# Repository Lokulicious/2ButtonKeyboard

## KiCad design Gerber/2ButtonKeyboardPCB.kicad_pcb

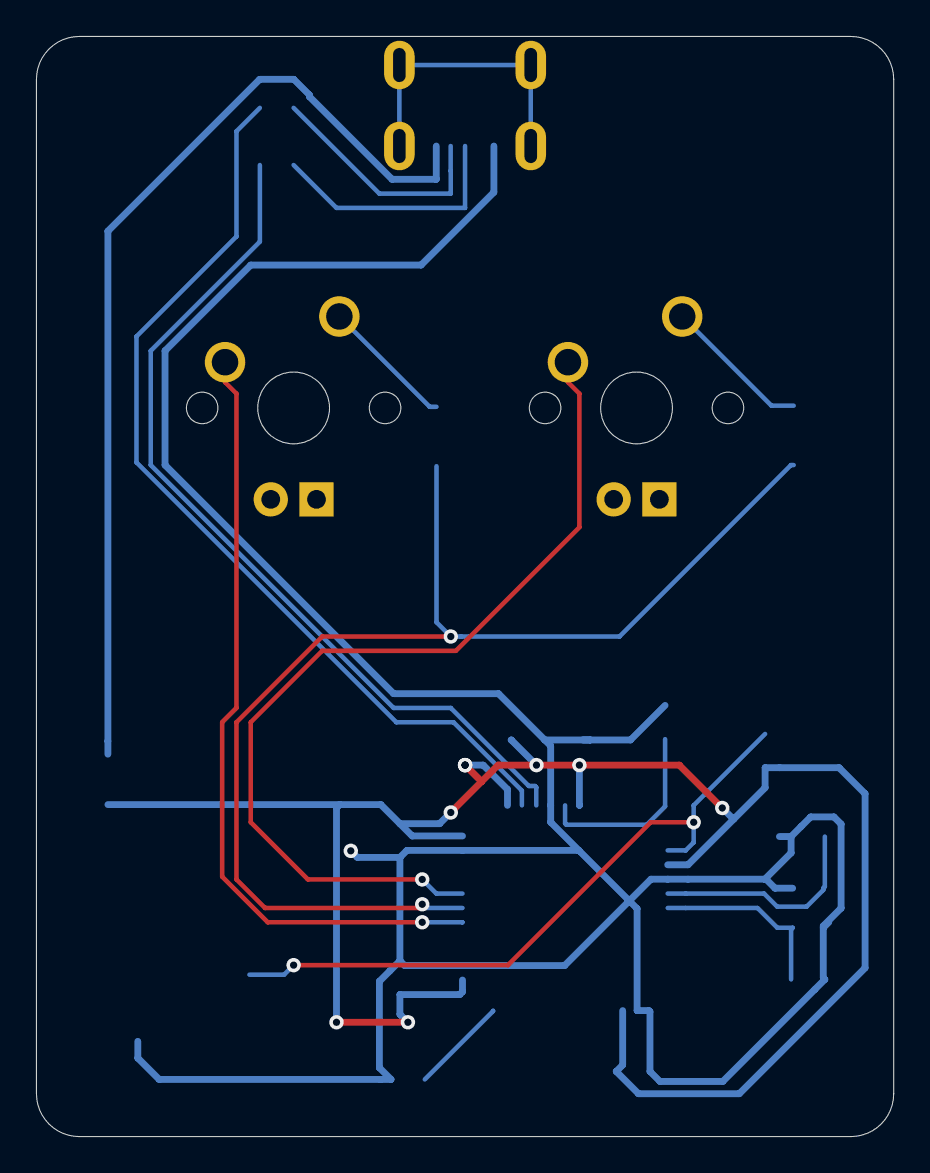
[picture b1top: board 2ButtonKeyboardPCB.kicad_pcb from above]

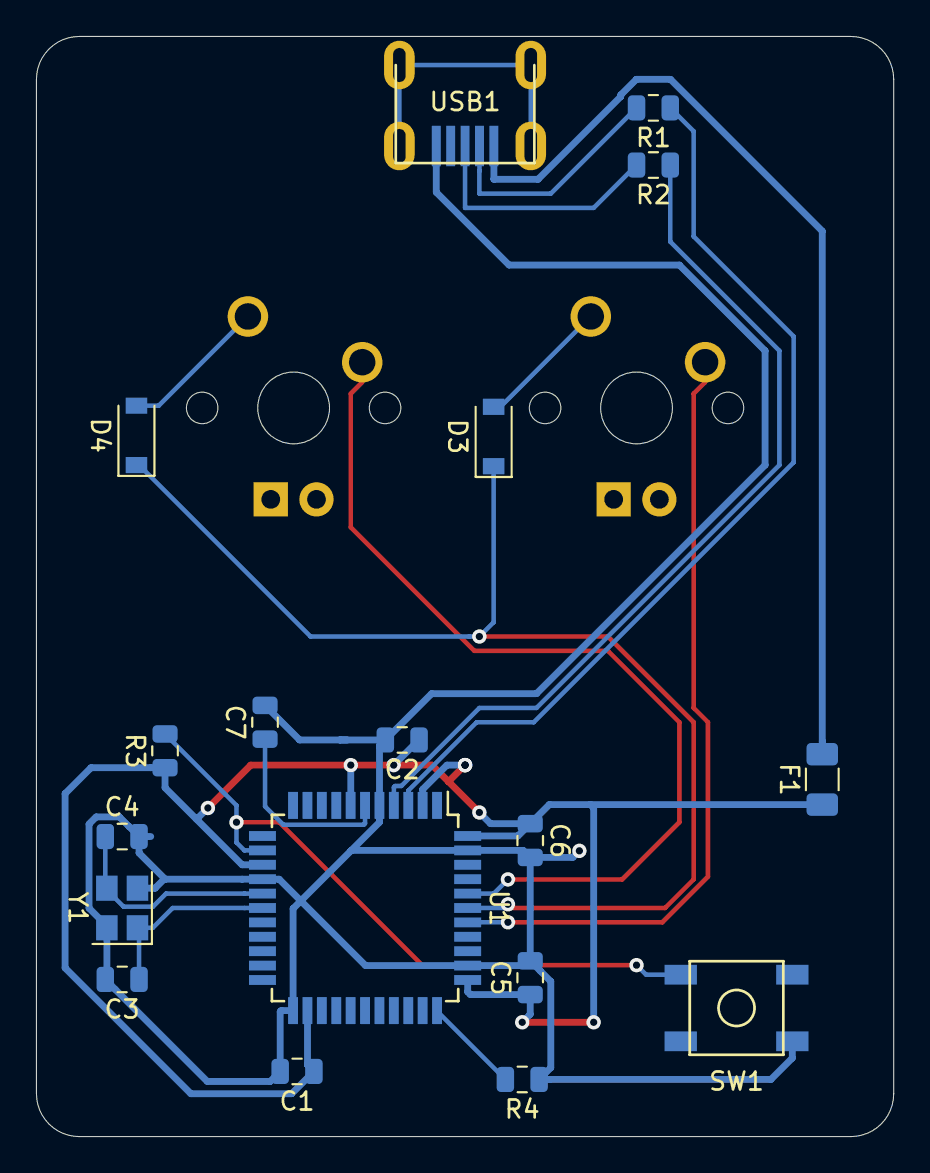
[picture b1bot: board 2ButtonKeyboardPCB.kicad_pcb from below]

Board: 2 copper layers, 47.6 x 61.1 mm, 20 parts (18 on the bottom side), 17 nets.

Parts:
C1, C2, C5: 0.1uF; C_0805_2012Metric
C3, C4: 22pF; C_0805_2012Metric
C6: 10uF; C_0805_2012Metric
C7: 1uF; C_0805_2012Metric
D3, D4: D_Small; D_SOD-123
F1: Polyfuse_Small; Fuse_1206_3216Metric
MX3, MX4: MX-NoLED; MXOnly-1U
R1, R2: 22; R_0805_2012Metric
R3, R4: 10k; R_0805_2012Metric
SW1: SW_Push; SKQG-1155865
U1: ATmega32U4-AU; TQFP-44_10x10mm_P0.8mm
USB1: Molex-0548190589
Y1: 16MHz; Crystal_SMD_3225-4Pin_3.2x2.5mm

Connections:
+5V: C1.1, C2.1, C5.1, C6.1, F1.1, R3.1, U1.2, U1.7, U1.14, U1.24, U1.34, U1.44
COL0: MX3.1, U1.38
COL1: MX4.1, U1.40
D+: R2.2, USB1.3
D-: R1.2, USB1.4
GND: C1.2, C2.2, C3.2, C4.2, C5.2, C6.2, C7.2, R4.1, SW1.1, U1.5, U1.15, U1.23, U1.35, U1.43, USB1.1, Y1.2, Y1.4
unnamed: C3.1, U1.17, Y1.1
unnamed: C4.1, U1.16, Y1.3
unnamed: C7.1, U1.6
unnamed: D3.2, MX3.2
unnamed: D4.2, MX4.2
unnamed: R1.1, U1.3
unnamed: R2.1, U1.4
unnamed: R3.2, SW1.2, U1.13
unnamed: R4.2, U1.33
ROW0: D3.1, D4.1, U1.39
VCC: F1.2, USB1.5

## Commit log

2023-01-15 Created Project
2023-01-15 Add submodules
2023-01-15 Added Libraries
2023-01-15 Schematic part 1
2023-01-15 Schematic
2023-01-15 SchematicFootprints
2023-01-15 Pcb Layout and Routing
2023-01-16 Pcb Routing Update
